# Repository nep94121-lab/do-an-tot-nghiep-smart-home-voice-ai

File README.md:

# Smart Home Voice AI (`v3.8.0` / `v1.0`) — Trợ Lý Nhà Thông Minh Giọng Nói Tiếng Việt

> **TRẠNG THÁI HOÀN THIỆN HỆ THỐNG — SẴN SÀNG CẮM PHẦN CỨNG LÀ CHẠY:**
> Toàn bộ **máy chủ Backend FastAPI (`backend/`)**, **giao diện Web 3D Digital Twin & Mobile PWA (`web/`)**, **ứng dụng Android gốc (`app/`)** và **firmware ESP8266 (`firmware/`)** đã **hoàn thiện 100%** và được kiểm thử đầy đủ.
> **Chỉ còn duy nhất bước cuối cùng ở hiện trường:** cắm bo mạch **NodeMCU ESP8266 v2 Amica** thật qua cáp Micro-USB, chạy **1 lệnh PowerShell** nạp firmware & nhập Wi-Fi lúc chạy (runtime, lưu vào LittleFS, không bao giờ lưu mật khẩu trong mã nguồn), gắn lên mạch **PCB Hub DIY v3** và cấp nguồn `5V 2A` là hệ thống hoạt động hoàn chỉnh.
>
> **Hướng dẫn nạp USB & cài Wi-Fi runtime thống nhất (Đọc ngay tại đây):**
> [`docs/huong_dan/CAI_DAT_WIFI_VA_NAP_USB.md`](docs/huong_dan/CAI_DAT_WIFI_VA_NAP_USB.md)

Trợ lý AI điều khiển nhà thông minh phản hồi tức thì bằng **100% tiếng Việt** (giọng `Aoede` duy nhất trên `gemini-3.8-live`), tích hợp **FastAPI Backend (`v3.8.0`) + SQLite WAL (25 bảng)**, **Web 3D Digital Twin (Three.js `r128`)**, **ứng dụng Android gốc (Kotlin + Jetpack Compose)**, **phần cứng PCB-Direct Hub DIY v3 (`100 × 80 × 1.6 mm`, không dùng breadboard trắng)** cùng **NodeMCU ESP8266 v2 Amica (`48.26 × 25.40 mm`, CP2102)** và **bộ vỏ nhà in 3D lắp mộng `agyhw14` (`16` bàn in, `660.64 g` PLA)**.

---

## 1. Hợp Đồng Phần Cứng Khóa Cứng (14 Module Vật Lý $\rightarrow$ 6 Thiết Bị + 3 Cảm Biến)

Hệ thống gồm **14 khối/module vật lý ngoài bo** (cộng `NodeMCU v2 Amica` và `PCB Hub DIY v3` thành `16` thành phần trong mô hình 3D) ánh xạ sang đúng **6 thiết bị chấp hành + 3 cảm biến** trên 10 chân **NodeMCU ESP8266 v2 Amica (`48.26 × 25.40 mm`, hàng chân `0.9"` — không dùng v3 LoLin)** cắm trực tiếp lên mạch **PCB Hub DIY v3 (`100 × 80 × 1.6 mm`, `51 footprints`, `0 ERC / 0 DRC`)** với **toàn bộ `C1–C9` (gồm `C8 100 nF` & `C9 100 µF 16V`) và `D1–D2 (1N4007)` hàn trực tiếp trên PCB**, cùng **40/40 dây nối `<= 30 cm` (`3.84 – 27.48 cm`)**.
**Chính sách phạm vi chốt:** **Không dùng breadboard trắng; không hỗ trợ quạt (`fan`), điều hòa (`ac`) hay hồng ngoại (`IR` / `VS1838B`).** Xem bảng ánh xạ chi tiết 14 module tại [`docs/phan_cung/TONG_QUAN_PHAN_CUNG_VA_IN_3D.md`](docs/phan_cung/TONG_QUAN_PHAN_CUNG_VA_IN_3D.md).

| Loại | Mã định danh | Tên hiển thị & Khối vật lý đi kèm | Chân ESP8266 | Quyền tối thiểu |
| :--- | :--- | :--- | :---: | :--- |
| Thiết bị | `main_door` | Cửa chính (Servo SG90 đồng trục không vít/keo) | `D1` (`GPIO5`) | Cấp 1 (Chủ nhà) |
| Thiết bị | `alarm_siren` | Còi báo động (Buzzer 5V `TMB12A05` + `Q1 S8050` + `D2`) | `D8` (`GPIO15`) | Cấp 1 (Chủ nhà) |
| Thiết bị | `garden_pump` | Bơm tưới cây (Relay 1 xanh 5V + Bơm chìm 3–6V + `D1`) | `D6` (`GPIO12`) | Cấp 2 (Thành viên) |
| Thiết bị | `speaker_amp` | Loa phản hồi (Relay 2 opto đỏ + `PAM8403` + Loa `28mm` + PWM `D3`) | `D7` (`GPIO13`) | Cấp 2 (Thành viên) |
| Thiết bị | `living_room_light` | Đèn phòng khách (LED 5mm + `R1 220Ω`) | `D0` (`GPIO16`) | Cấp 3 (Khách) |
| Thiết bị | `bedroom_light` | Đèn phòng ngủ (LED 5mm Active-LOW + `R2 220Ω` + `R7 10kΩ`) | `D4` (`GPIO2`) | Cấp 3 (Khách) |
| Cảm biến | `dht11` | Nhiệt độ (°C) & Độ ẩm không khí (%) (`DHT11` 3 chân) | `D2` (`GPIO4`) | Mọi cấp đã đăng nhập |
| Cảm biến | `soil_moisture` | Độ ẩm đất (`LM393` cấp `3.3V` + đầu dò `YL-69`) | `A0` (`ADC0`) | Mọi cấp đã đăng nhập |
| Cảm biến | `ky037` | Cảm biến âm thanh / tiếng vỗ tay (`KY-037/038 DO`, `3.3V`) | `D5` (`GPIO14`) | Mọi cấp đã đăng nhập |

---

## 2. Cấu Trúc Thư Mục Dự Án

Giữ nguyên toàn bộ các thư mục mã nguồn cốt lõi và tổ chức gọn tầng tài liệu theo nhóm chức năng rõ ràng:

```text
.
├── backend/                     # FastAPI v3.8.0, SQLite WAL (25 bảng), MQTT, SSE/WS, RBAC 3 tầng, Gemini Live Voice AI
├── web/                         # Web Dashboard 3D Digital Twin (Three.js r128), Mobile PWA (/app), /wokwi, /automation, /auth, /logs
├── app/                         # Ứng dụng Android gốc (Kotlin 2.3.20 + Jetpack Compose 1.10.4, minSdk 26, Lightbuild)
├── firmware/                    # Firmware NodeMCU ESP8266 v2 Amica (LittleFS Wi-Fi runtime + Offline FSM A1–A4) & Wokwi
├── hardware/
│   ├── flash_and_setup.ps1      # Script 1 lệnh nạp USB + nhập Wi-Fi runtime an toàn (ẩn mật khẩu) + SELF_TEST
│   ├── wiring_contract.py       # SSOT 40 dây nối, 15 đầu nối PCB J1–J15 & linh kiện bảo vệ C1–C9, D1–D2
│   ├── component_dimensions_ssot.py # SSOT kích thước datasheet 14 module + 2 bo lõi & thông số Servo SG90
│   ├── wire_lengths.json        # Chiều dài 3D thực tế 40/40 dây <= 30 cm (3.84–27.48 cm)
│   ├── kicad/                   # PCB Hub DIY v3 (100×80×1.6 mm, 51 footprints, 0 ERC / 0 DRC) & lắp ghép 3D
│   ├── mica/                    # Thiết kế vỏ nhà Mica 3mm cắt laser (FreeCAD 1.1.4)
│   ├── in 3 d/                  # Bộ in 3D v2 nhẹ hóa agyhw14: 16 bàn .3mf nhúng sẵn cấu hình, 660.64 g PLA, 0 support
│   └── blender/                 # Cảnh 3D tổng thể & 40 tuyến dây nối (Blender 5.2.2 LTS)
├── docs/
│   ├── kien_truc/               # Kiến trúc hệ thống (Mermaid), Công nghệ & Phiên bản thực đo, ERD SQLite 25 bảng, Repo Map
│   ├── huong_dan/               # Hướng dẫn thống nhất nạp USB & Wi-Fi runtime, Vận hành & Triển khai Production
│   ├── phan_cung/               # Tổng quan phần cứng & In 3D, WIRING_TABLE, WIRE_LIST_LENGTHS, DIMENSIONS_AUDIT, diy_pcb/, mica/
│   ├── bao_cao/                 # Hồ sơ Báo cáo Đồ án Tốt nghiệp (.docx / .pdf / script sinh / LOGO_SOURCES.md)
│   ├── luu_tru/                 # Tài liệu khảo sát & lịch sử giai đoạn đầu (chỉ lưu trữ, không dùng vận hành)
│   ├── screenshots/             # 13 ảnh chụp màn hình kiểm chứng Web, Mobile PWA, Android & Sơ đồ 2D
│   ├── HARDWARE_BUILD_GUIDE.md  # Chỉ mục chế tạo PCB-direct, cắt Mica / In 3D & đấu nối
│   └── TIER_PERMISSIONS.md      # Bảng phân quyền 3 tầng khóa cứng cho 6 thiết bị
├── tests/                       # Bộ kiểm thử tự động pytest (Backend, RBAC, Voice agyfix11, PCB/In 3D agyhw12–14)
├── scripts/                     # Tiện ích sinh tài liệu dây nối, kiểm định kích thước & công cụ bảo trì
├── specs/                       # Đặc tả kỹ thuật tham chiếu
├── test_audio/                  # Bộ mẫu âm thanh tiếng Việt kiểm thử giọng nói
├── USER_GUIDE.md                # Hướng dẫn sử dụng chi tiết cho người dùng cuối
├── KE_HOACH_DO_AN_TOT_NGHIEP.md # Hồ sơ tiến độ & trạng thái hoàn thiện đồ án
├── KNOWN_ISSUES.md              # Danh mục vấn đề nhỏ đã biết & giải pháp tạm thời
└── CHANGELOG.md                 # Nhật ký phát hành các phiên bản
```

---

## 3. Chỉ Mục Toàn Bộ Tài Liệu Dự Án

| Nhóm tài liệu | Tài liệu | Nội dung chính |
| :--- | :--- | :--- |
| **Cắm phần cứng & Wi-Fi** | [**Hướng dẫn nạp Firmware USB & Cài Wi-Fi Runtime**](docs/huong_dan/CAI_DAT_WIFI_VA_NAP_USB.md) | Quy trình 3 bước cắm USB $\rightarrow$ chạy `hardware/flash_and_setup.ps1` nhập Wi-Fi lưu LittleFS `/wifi_config.json` $\rightarrow$ cấp nguồn chạy, driver CP2102/CH340, chân boot-strap `D3/D4/D8`, xử lý sự cố |
| **Người dùng cuối** | [Hướng dẫn sử dụng (`USER_GUIDE.md`)](USER_GUIDE.md) | Phân quyền 3 cấp, mã mời QR dùng 1 lần, Web 3D `/`, Mobile `/app`, Tự động hóa `/automation`, giọng nói tiếng Việt, ứng dụng Android, `/wokwi` & chế độ ngoại tuyến |
| **Kiến trúc & Phiên bản** | [Kiến trúc hệ thống chi tiết (`KIEN_TRUC_HE_THONG.md`)](docs/kien_truc/KIEN_TRUC_HE_THONG.md) | Kiến trúc toàn bộ phân hệ Backend, SQLite WAL, MQTT, SSE/WS, Web 3D, Android, ESP8266, Gemini Live `agyfix11`, RBAC & 4 sơ đồ tuần tự Mermaid |
| **Kiến trúc & Phiên bản** | [Công nghệ & Phiên bản phần mềm (`CONG_NGHE_VA_PHIEN_BAN.md`)](docs/kien_truc/CONG_NGHE_VA_PHIEN_BAN.md) | Bảng phiên bản thực đo đầy đủ của Python, FastAPI, SQLite, Three.js, Kotlin/Compose, PlatformIO, KiCad, FreeCAD, Blender, PrusaSlicer, Playwright, Tailscale, Vercel |
| **Kiến trúc & Phiên bản** | [Sơ đồ CSDL SQLite 25 bảng (`DATABASE_SCHEMA_ERD.md`)](docs/kien_truc/DATABASE_SCHEMA_ERD.md) | Sơ đồ thực thể kết hợp (ERD Mermaid) đủ 25 bảng 3NF và cơ chế cách ly 2 bể tự động hóa |
| **Kiến trúc & Phiên bản** | [Bảng phân quyền 3 tầng (`docs/TIER_PERMISSIONS.md`)](docs/TIER_PERMISSIONS.md) · [Bản đồ mã nguồn (`REPO_MAP.md`)](docs/kien_truc/REPO_MAP.md) | Ma trận quyền 3 cấp khóa cứng 6 thiết bị & chỉ mục cấu trúc mã nguồn hiện hành |
| **Vận hành & Triển khai** | [Hướng dẫn vận hành & triển khai (`VAN_HANH_VA_TRIEN_KHAI.md`)](docs/huong_dan/VAN_HANH_VA_TRIEN_KHAI.md) | Biến môi trường `.env` (chỉ tên biến), chạy cổng `8088`, Tailscale Funnel, Vercel redirect, backup/restore SQLite WAL, `DEPLOY.lock`, quy trình `pytest` + Playwright + Android APK |
| **Phần cứng & In 3D** | [Tổng quan phần cứng 14 module & In 3D (`TONG_QUAN_PHAN_CUNG_VA_IN_3D.md`)](docs/phan_cung/TONG_QUAN_PHAN_CUNG_VA_IN_3D.md) | Bảng ánh xạ SSOT 14 module vật lý + 2 bo lõi sang 6 thiết bị + 3 cảm biến, PCB Hub DIY v3, 40 dây `<= 30 cm`, bộ in 3D 16 bàn `660.64 g` |
| **Phần cứng & In 3D** | [Chỉ mục chế tạo phần cứng (`docs/HARDWARE_BUILD_GUIDE.md`)](docs/HARDWARE_BUILD_GUIDE.md) · [Bảng 40 dây (`WIRING_TABLE.md`)](docs/phan_cung/WIRING_TABLE.md) · [Chiều dài dây (`WIRE_LIST_LENGTHS.md`)](docs/phan_cung/WIRE_LIST_LENGTHS.md) | Hồ sơ gia công KiCad [`diy_pcb/`](docs/phan_cung/diy_pcb/), kiểm định kích thước [`DIMENSIONS_AUDIT.md`](docs/phan_cung/DIMENSIONS_AUDIT.md), linh kiện [`DANH_SACH_LINH_KIEN_HIEN_CO_VA_CAN_MUA.md`](docs/phan_cung/DANH_SACH_LINH_KIEN_HIEN_CO_VA_CAN_MUA.md), bộ in 3D [`hardware/in 3 d/README.md`](hardware/in%203%20d/README.md) |
| **Firmware ESP8266** | [Tài liệu Firmware (`firmware/README.md`)](firmware/README.md) · [Bản nạp USB cho `/wokwi`](docs/phan_cung/HUONG_DAN_NAP_FIRMWARE_USB.md) | Chi tiết sơ đồ 10 chân boot-safe và cơ chế dự phòng ngoại tuyến Addendum A1–A4 |
| **Quản trị & Lịch sử** | [Hồ sơ Đồ án (`KE_HOACH_DO_AN_TOT_NGHIEP.md`)](KE_HOACH_DO_AN_TOT_NGHIEP.md) · [Vấn đề đã biết (`KNOWN_ISSUES.md`)](KNOWN_ISSUES.md) · [Nhật ký (`CHANGELOG.md`)](CHANGELOG.md) · [Kho lưu trữ cũ (`docs/luu_tru/`)](docs/luu_tru/README.md) | Trạng thái hoàn thiện tổng thể, danh mục giới hạn nhỏ fail-closed, lịch sử phát hành và tài liệu khảo sát giai đoạn đầu |

---

## 4. Khởi Chạy Nhanh (Quick Start)

### 4.1. Cài đặt phụ thuộc & khởi động máy chủ Backend (`:8088`)
```powershell
pip install -r requirements.txt
# Tạo tệp .env ở thư mục gốc (không commit Git) với GEMINI_API_KEY (xem VAN_HANH_VA_TRIEN_KHAI.md)
python -X utf8 -m uvicorn backend.server:app --host 0.0.0.0 --port 8088
```
Truy cập trình duyệt tại `http://127.0.0.1:8088/` (máy tính) hoặc `http://127.0.0.1:8088/app` (di động).

### 4.2. Nạp Firmware ESP8266 & cấu hình Wi-Fi Runtime qua USB (1 lệnh)
```powershell
# Kiểm tra toolchain PlatformIO, driver CP210x/CH340, cổng COM và biên dịch khô (không nạp)
powershell -NoProfile -ExecutionPolicy Bypass -File hardware\flash_and_setup.ps1 -DryRun

# Cắm NodeMCU ESP8266 qua cáp Micro-USB, nạp firmware + nhập Wi-Fi runtime ẩn mật khẩu + SELF_TEST
powershell -NoProfile -ExecutionPolicy Bypass -File hardware\flash_and_setup.ps1
```
Xem chi tiết từng bước và bảng khắc phục sự cố tại [`docs/huong_dan/CAI_DAT_WIFI_VA_NAP_USB.md`](docs/huong_dan/CAI_DAT_WIFI_VA_NAP_USB.md).

### 4.3. Biên dịch ứng dụng Android (`app/`) & chạy kiểm thử (`pytest`)
```powershell
# Biên dịch ứng dụng Android gốc (Kotlin 2.3.20 + Jetpack Compose, minSdk 26)
Set-Location app
lightbuild --plain build app

# Kiểm thử hồi quy phần cứng, PCB-Direct, Servo và In 3D (chạy tại thư mục gốc)
python -m pytest -q --timeout=120 \
  tests/test_hw_contract_6devices_20261120.py \
  tests/test_pcbdirect_agyhw12.py \
  tests/test_servodoor_agyhw13.py \
  tests/test_lessplastic_agyhw14.py
```

### 4.4. Tóm tắt Phần cứng PCB-Direct & Bộ In 3D `agyhw14`
- **PCB Hub DIY v3 (`100 × 80 × 1.6 mm`, 1 lớp `B.Cu`, không dùng breadboard trắng):** `51 footprints`, `0 ERC / 0 DRC`, toàn bộ `C1–C9` & `D1–D2` hàn trực tiếp trên bo.
- **Hệ thống dây nối (`40/40 <= 30 cm`):** Ngắn nhất `3.84 cm`, dài nhất `27.48 cm`, tổng `654.99 cm` (`10` sợi 10 cm, `18` sợi 20 cm, `12` sợi 30 cm).
- **Vỏ nhà In 3D v2 (`agyhw14`, `180×200×250 mm`):** **`16` bàn in `.3mf`** nhúng sẵn thông số (`9% Gyroid`, `2/3` thành, `0% support`), **`51` chi tiết / `83` bản thể**, **`660.64 g` PLA** (`-36.77%` so với `1044.86 g`), thời gian in `73g 23p 49s`, `0` va chạm 3D BRep, cơ cấu cửa Servo SG90 đồng trục dự trữ mô-men `14.56×`.

---

## 5. Thư Viện Ảnh Chụp Kiểm Chứng (`docs/screenshots/`)

| Ảnh chụp (`docs/screenshots/`) | Nội dung minh họa |
| :--- | :--- |
| [`01_dashboard_3d_desktop_1440x900.png`](docs/screenshots/01_dashboard_3d_desktop_1440x900.png) | Giao diện Web Dashboard 3D Digital Twin & 6 thiết bị (`1440×900`) |
| [`02_dashboard_3d_desktop_1366x768.png`](docs/screenshots/02_dashboard_3d_desktop_1366x768.png) | Giao diện Web Dashboard 3D Digital Twin trên màn hình laptop (`1366×768`) |
| [`03_dashboard_3d_mobile_390x844.png`](docs/screenshots/03_dashboard_3d_mobile_390x844.png) | Giao diện Web Dashboard đáp ứng di động (`390×844`) |
| [`04_automation_panel_1440x900.png`](docs/screenshots/04_automation_panel_1440x900.png) | Trang Tự động hóa (`/automation`): luật tổ hợp `AND`/`OR`, lịch tuần & hẹn giờ |
| [`05_wokwi_circuit_1440x900.png`](docs/screenshots/05_wokwi_circuit_1440x900.png) | Trang Hướng dẫn Đấu nối PCB-Direct 10 chân ESP8266 & PCB Hub `100×80 mm` (`/wokwi`) |
| [`06_auth_rbac_1440x900.png`](docs/screenshots/06_auth_rbac_1440x900.png) | Trang Quản lý Phiên & Phân quyền 3 tầng (`/auth`) |
| [`07_logs_audit_1440x900.png`](docs/screenshots/07_logs_audit_1440x900.png) | Trang Nhật ký Hệ thống dành riêng cho Chủ nhà Cấp 1 (`/logs`) |
| [`08_mobile_pwa_390x844.png`](docs/screenshots/08_mobile_pwa_390x844.png) | Giao diện Ứng dụng Web Di động PWA (`/app`, `390×844`) |
| [`09_android_auth_gate.png`](docs/screenshots/09_android_auth_gate.png) | Ứng dụng Android gốc: cổng xác thực khi chưa đăng nhập & nút Quét mã QR |
| [`10_android_home_live.png`](docs/screenshots/10_android_home_live.png) | Ứng dụng Android gốc: màn hình chính & thẻ thông số cảm biến thời gian thực |
| [`11_android_devices_6locked.png`](docs/screenshots/11_android_devices_6locked.png) | Ứng dụng Android gốc: danh sách 6 thiết bị chấp hành theo hợp đồng khóa cứng |
| [`12_android_voice_vi.png`](docs/screenshots/12_android_voice_vi.png) | Ứng dụng Android gốc: trợ lý giọng nói tiếng Việt đồng bộ máy chủ |
| [`13_hardware_wiring_2d.png`](docs/screenshots/13_hardware_wiring_2d.png) | Sơ đồ đấu nối tổng thể 2D PCB-Direct 40 dây & 15 đầu nối PCB Hub DIY v3 (`100×80 mm`) |

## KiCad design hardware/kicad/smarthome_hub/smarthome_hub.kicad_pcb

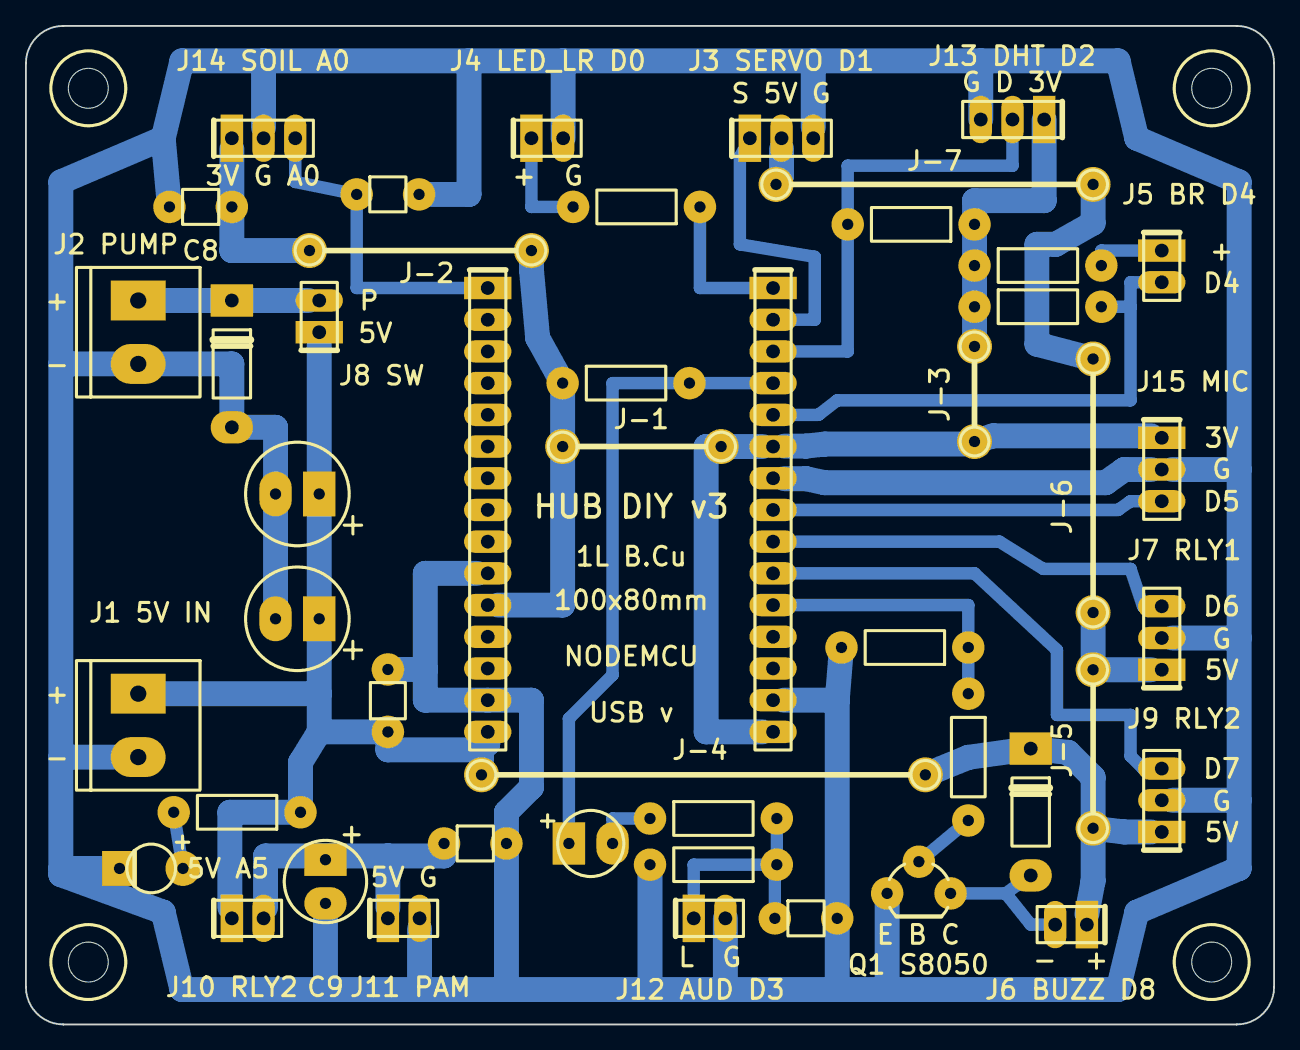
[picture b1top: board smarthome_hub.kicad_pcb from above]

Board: 2 copper layers, 100.0 x 80.0 mm, 51 parts (0 on the bottom side), 29 nets.

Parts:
C1, C2: 470uF 16V; CP_Radial_D8.0mm_P3.50mm_DIY
C3, C6, C7, C8: 100nF; C_Disc_D5.0mm_P5.00mm_DIY
C4: 10uF 16V; CP_Radial_D5.0mm_P3.50mm_DIY
C5: 10nF; C_Disc_D5.0mm_P5.00mm_DIY
C9: 100uF 16V; CP_Radial_D6.3mm_P3.50mm_DIY
D1, D2: 1N4007; D_DO41_P10.16mm_DIY
D3: LED_PWR_GRN; LED_D3.0mm_P5.08mm_DIY
H1, H2, H3, H4: M3_3.2mm; MountingHole_3.2mm_M3_DIY
J1: PWR_5V_IN; TerminalBlock_MKDS_1x02_P5.08mm_DIY
J2: PUMP_OUT; TerminalBlock_MKDS_1x02_P5.08mm_DIY
J3: SERVO_D1; PinHeader_1x03_P2.54mm_DIY
J4: LED_LR_D0; PinHeader_1x02_P2.54mm_DIY
J5: LED_BR_D4; PinHeader_1x02_P2.54mm_DIY
J6: BUZZ_D8; PinHeader_1x02_P2.54mm_DIY
J7: RLY1_PUMP_D6; PinHeader_1x03_P2.54mm_DIY
J8: RLY1_SW; PinHeader_1x02_P2.54mm_DIY
J9: RLY2_AMP_D7; PinHeader_1x03_P2.54mm_DIY
J10: RLY2_SW; PinHeader_1x02_P2.54mm_DIY
J11: PAM8403_PWR; PinHeader_1x02_P2.54mm_DIY
J12: AUDIO_D3; PinHeader_1x02_P2.54mm_DIY
J13: DHT11_D2; PinHeader_1x03_P2.54mm_DIY
J14: SOIL_A0; PinHeader_1x03_P2.54mm_DIY
J15: KY037_D5; PinHeader_1x03_P2.54mm_DIY
JP1, JP5: JUMPER_12.70mm; WireJumper_P12.70mm_DIY
JP2: JUMPER_17.78mm; WireJumper_P17.78mm_DIY
JP3: JUMPER_7.62mm; WireJumper_P7.62mm_DIY
JP4: JUMPER_35.56mm; WireJumper_P35.56mm_DIY
JP6: JUMPER_20.32mm; WireJumper_P20.32mm_DIY
JP7: JUMPER_25.40mm; WireJumper_P25.40mm_DIY
Q1: S8050; TO-92_Wide_DIY
R1, R2: 220R; R_Axial_P10.16mm_DIY
R3, R4, R7, R9: 10k; R_Axial_P10.16mm_DIY
R5, R6: 2.2k; R_Axial_P10.16mm_DIY
R8, R10: 1k; R_Axial_P10.16mm_DIY
U1: NodeMCU_Left_1x15; PinSocket_1x15_P2.54mm_DIY
U2: NodeMCU_Right_1x15; PinSocket_1x15_P2.54mm_DIY

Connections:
+3V3: JP1.1, JP2.1, R4.1, U1.11
+5V: C1.1, C2.1, C3.1, J1.1, J8.1, J10.1, JP4.1, R8.1, U1.15
/+3V3_R: J15.1, JP1.2, JP3.1, U2.6, U2.15
/+3V3_SOIL: C8.1, J14.1, JP2.2
/+3V3_TOP: J13.1, JP3.2, R2.1, R3.1, R7.1
/+5V_RLY1: J7.1, JP5.2, JP6.1
/+5V_RLY2: D2.1, J6.1, J9.1, JP4.2, JP5.1
/+5V_SERVO: J3.2, JP7.2
/+5V_TOP: JP6.2, JP7.1
/A0_SOIL: C7.1, J14.3, U1.1
/AMP_5V: C6.1, C9.1, J10.2, J11.1
/AUD_OUT: C5.1, J12.1, R5.2, R6.1
/BUZZ_BASE: Q1.2, R10.2
/BUZZ_K: D2.2, J6.2, Q1.3
/D0_LED_LR: R1.1, U2.1
/D1_SERVO: J3.1, U2.2
/D2_DHT11: J13.2, R3.2, U2.3
/D3_AUDIO_PWM: C4.1, R4.2, U2.4
/D4_LED_BR: J5.2, R7.2, U2.5
/D5_MIC_DO: J15.3, U2.8
/D6_RLY1_PUMP: J7.3, U2.9
/D7_RLY2_AMP: J9.3, U2.10
/D8_BUZZER: R9.1, R10.1, U2.11
/PUMP_5V: D1.1, J2.1, J8.2
GND: C1.2, C2.2, C3.2, C5.2, C6.2, C7.2, C8.2, C9.2, D1.2, D3.1, J1.2, J2.2, J3.3, J4.2, J7.2, J9.2, J11.2, J12.2, J13.3, J14.2, J15.2, Q1.1, R6.2, R9.2, U1.10, U1.14, U2.7, U2.14
unnamed: C4.2, R5.1
unnamed: D3.2, R8.2
unnamed: J4.1, R1.2
unnamed: J5.1, R2.2

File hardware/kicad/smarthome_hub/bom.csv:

"Refs","Value","Footprint","Qty","DNP"
"C1","470uF 16V","DIY_Hub:CP_Radial_D8.0mm_P3.50mm_DIY","1",""
"C2","470uF 16V","DIY_Hub:CP_Radial_D8.0mm_P3.50mm_DIY","1",""
"C3","100nF","DIY_Hub:C_Disc_D5.0mm_P5.00mm_DIY","1",""
"C4","10uF 16V","DIY_Hub:CP_Radial_D5.0mm_P3.50mm_DIY","1",""
"C5","10nF","DIY_Hub:C_Disc_D5.0mm_P5.00mm_DIY","1",""
"C6","100nF","DIY_Hub:C_Disc_D5.0mm_P5.00mm_DIY","1",""
"C7","100nF","DIY_Hub:C_Disc_D5.0mm_P5.00mm_DIY","1",""
"C8","100nF","DIY_Hub:C_Disc_D5.0mm_P5.00mm_DIY","1",""
"C9","100uF 16V","DIY_Hub:CP_Radial_D6.3mm_P3.50mm_DIY","1",""
"D1","1N4007","DIY_Hub:D_DO41_P10.16mm_DIY","1",""
"D2","1N4007","DIY_Hub:D_DO41_P10.16mm_DIY","1",""
"D3","LED_PWR_GRN","DIY_Hub:LED_D3.0mm_P5.08mm_DIY","1",""
"H1","M3_3.2mm","DIY_Hub:MountingHole_3.2mm_M3_DIY","1",""
"H2","M3_3.2mm","DIY_Hub:MountingHole_3.2mm_M3_DIY","1",""
"H3","M3_3.2mm","DIY_Hub:MountingHole_3.2mm_M3_DIY","1",""
"H4","M3_3.2mm","DIY_Hub:MountingHole_3.2mm_M3_DIY","1",""
"J1","PWR_5V_IN","DIY_Hub:TerminalBlock_MKDS_1x02_P5.08mm_DIY","1",""
"J2","PUMP_OUT","DIY_Hub:TerminalBlock_MKDS_1x02_P5.08mm_DIY","1",""
"J3","SERVO_D1","DIY_Hub:PinHeader_1x03_P2.54mm_DIY","1",""
"J4","LED_LR_D0","DIY_Hub:PinHeader_1x02_P2.54mm_DIY","1",""
"J5","LED_BR_D4","DIY_Hub:PinHeader_1x02_P2.54mm_DIY","1",""
"J6","BUZZ_D8","DIY_Hub:PinHeader_1x02_P2.54mm_DIY","1",""
"J7","RLY1_PUMP_D6","DIY_Hub:PinHeader_1x03_P2.54mm_DIY","1",""
"J8","RLY1_SW","DIY_Hub:PinHeader_1x02_P2.54mm_DIY","1",""
"J9","RLY2_AMP_D7","DIY_Hub:PinHeader_1x03_P2.54mm_DIY","1",""
"J10","RLY2_SW","DIY_Hub:PinHeader_1x02_P2.54mm_DIY","1",""
"J11","PAM8403_PWR","DIY_Hub:PinHeader_1x02_P2.54mm_DIY","1",""
"J12","AUDIO_D3","DIY_Hub:PinHeader_1x02_P2.54mm_DIY","1",""
"J13","DHT11_D2","DIY_Hub:PinHeader_1x03_P2.54mm_DIY","1",""
"J14","SOIL_A0","DIY_Hub:PinHeader_1x03_P2.54mm_DIY","1",""
"J15","KY037_D5","DIY_Hub:PinHeader_1x03_P2.54mm_DIY","1",""
"JP1","JUMPER_12.70mm","DIY_Hub:WireJumper_P12.70mm_DIY","1",""
"JP2","JUMPER_17.78mm","DIY_Hub:WireJumper_P17.78mm_DIY","1",""
"JP3","JUMPER_7.62mm","DIY_Hub:WireJumper_P7.62mm_DIY","1",""
"JP4","JUMPER_35.56mm","DIY_Hub:WireJumper_P35.56mm_DIY","1",""
"JP5","JUMPER_12.70mm","DIY_Hub:WireJumper_P12.70mm_DIY","1",""
"JP6","JUMPER_20.32mm","DIY_Hub:WireJumper_P20.32mm_DIY","1",""
"JP7","JUMPER_25.40mm","DIY_Hub:WireJumper_P25.40mm_DIY","1",""
"Q1","S8050","DIY_Hub:TO-92_Wide_DIY","1",""
"R1","220R","DIY_Hub:R_Axial_P10.16mm_DIY","1",""
"R2","220R","DIY_Hub:R_Axial_P10.16mm_DIY","1",""
"R3","10k","DIY_Hub:R_Axial_P10.16mm_DIY","1",""
"R4","10k","DIY_Hub:R_Axial_P10.16mm_DIY","1",""
"R5","2.2k","DIY_Hub:R_Axial_P10.16mm_DIY","1",""
"R6","2.2k","DIY_Hub:R_Axial_P10.16mm_DIY","1",""
"R7","10k","DIY_Hub:R_Axial_P10.16mm_DIY","1",""
"R8","1k","DIY_Hub:R_Axial_P10.16mm_DIY","1",""
"R9","10k","DIY_Hub:R_Axial_P10.16mm_DIY","1",""
"R10","1k","DIY_Hub:R_Axial_P10.16mm_DIY","1",""
"U1","NodeMCU_Left_1x15","DIY_Hub:PinSocket_1x15_P2.54mm_DIY","1",""
"U2","NodeMCU_Right_1x15","DIY_Hub:PinSocket_1x15_P2.54mm_DIY","1",""

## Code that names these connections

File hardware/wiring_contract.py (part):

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
    # --- Device 1: Main Door Servo SG90 (J3 -> SG90) ---
    WireEntry("W03", "Main Door (SG90)", "J3", "1", "J3.1 (SERVO_D1)", "Orange",
              "sg90_servo", "SG90 Micro Servo", "PWM (Orange)", "D1 (U2.2)", "GPIO5", "D1_SERVO",
              "esp8266_smarthome.ino:56", "Dupont 1x3 F-M",
              "50Hz PWM control: 0 deg closed / 90 deg open (main_door)"),
    WireEntry("W04", "Main Door (SG90)", "J3", "2", "J3.2 (SERVO_D1)", "Red",
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              "esp8266_smarthome.ino:59,68", "Dupont 1x2 F-F",
              "Current-limited +3.3V via on-board R2 220R for boot-safe Active-LOW LED"),
    WireEntry("W09", "Bedroom LED", "J5", "2", "J5.2 (LED_BR_D4)", "White",
              "led_bedroom", "5mm LED (Bedroom)", "Cathode (-)", "D4 (U2.5)", "GPIO2", "D4_LED_BR",
              "esp8266_smarthome.ino:59,68", "Dupont 1x2 F-F",
              "Active-LOW sink (BEDROOM_LED_ACTIVE_LOW=true); on-board R7 10k pull-up keeps GPIO2 HIGH at boot"),

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              "esp8266_smarthome.ino:61,70", "Dupont 1x3 F-F",
              "Relay 1 module logic/coil ground"),
    WireEntry("W12", "Garden Pump (Relay 1)", "J7", "3", "J7.3 (RLY1_PUMP_D6)", "Green",
              "relay1_pump", "Relay 1 (Blue 5V 1-ch)", "IN", "D6 (U2.9)", "GPIO12", "D6_RLY1_PUMP",
              "esp8266_smarthome.ino:61,70", "Dupont 1x3 F-F",
              "Relay 1 trigger input (PUMP_RELAY_ACTIVE_LOW=false, active-HIGH)"),
    WireEntry("W13", "Garden Pump (Relay 1)", "J8", "1", "J8.1 (RLY1_SW)", "Red",
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              "esp8266_smarthome.ino:63,399", "Dupont 1x2 F-F",
              "+5V supply to TMB12A05 buzzer anode; protected by on-board D2 1N4007 flyback across J6.1-J6.2"),
    WireEntry("W18", "Alarm Siren (Buzzer)", "J6", "2", "J6.2 (BUZZ_D8)", "Orange",
              "buzzer_alarm", "Active 5V Buzzer (TMB12A05)", "Buzzer (-)", "D8 (U2.11) via Q1 S8050", "GPIO15 (NPN low-side)", "BUZZ_K",
              "esp8266_smarthome.ino:63,399", "Dupont 1x2 F-F",
              "Low-side switched by on-board Q1 (S8050 NPN) + R10 1k base resistor; R9 10k pull-down keeps GPIO15 LOW at boot"),

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              "esp8266_smarthome.ino:62,71", "Dupont 1x3 F-F",
              "Relay 2 module ground"),
    WireEntry("W21", "Speaker Amp (Relay 2)", "J9", "3", "J9.3 (RLY2_AMP_D7)", "Cyan",
              "relay2_speaker", "Relay 2 (Red Opto 5V, Jmp=H)", "IN", "D7 (U2.10)", "GPIO13", "D7_RLY2_AMP",
              "esp8266_smarthome.ino:62,71", "Dupont 1x3 F-F",
              "Active-HIGH trigger (SPEAKER_RELAY_ACTIVE_LOW=false); auto-off 1.5s after chime"),
    WireEntry("W22", "Speaker Amp (Relay 2)", "J10", "1", "J10.1 (RLY2_SW)", "Red",
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              "esp8266_smarthome.ino:62,163", "Dupont 1x2 F-F",
              "PAM8403 power ground"),
    WireEntry("W26", "Speaker Amp (Audio PWM)", "J12", "1", "J12.1 (AUDIO_D3)", "White",
              "pam8403_amp", "PAM8403 Audio Amplifier", "L (Audio In)", "D3 (U2.4) via C4/R5/R6/C5", "GPIO0", "AUD_OUT",
              "esp8266_smarthome.ino:58,166-184", "Dupont 1x2 F-F",
              "DC-blocked (C4 10uF) & RC-attenuated (R5/R6 2.2k, C5 10nF) audio; R4 10k pull-up + IDLE=INPUT for boot safety"),
    WireEntry("W27", "Speaker Amp (Audio PWM)", "J12", "2", "J12.2 (AUDIO_D3)", "Black",
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              "esp8266_smarthome.ino:57,83", "Dupont 1x3 F-F",
              "3.3V sensor supply"),
    WireEntry("W31", "DHT11 Sensor", "J13", "2", "J13.2 (DHT11_D2)", "Blue",
              "dht11_sensor", "DHT11 3-Pin Breakout", "DATA (OUT)", "D2 (U2.3)", "GPIO4", "D2_DHT11",
              "esp8266_smarthome.ino:57,83,544", "Dupont 1x3 F-F",
              "1-wire data bus with on-board R3 10k pull-up to +3V3"),
    WireEntry("W32", "DHT11 Sensor", "J13", "3", "J13.3 (DHT11_D2)", "Black",
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              "esp8266_smarthome.ino:14,60", "Dupont 1x3 F-F",
              "KY-037 ground (AO pin intentionally left NC / unconnected)"),
    WireEntry("W40", "Sound Sensor (KY-037)", "J15", "3", "J15.3 (KY037_D5)", "Yellow",
              "ky037_sound", "KY-037 / KY-038 Sound Module", "DO", "D5 (U2.8)", "GPIO14", "D5_MIC_DO",
              "esp8266_smarthome.ino:60,412", "Dupont 1x3 F-F",
              "Digital clap/loud-sound interrupt (RISING edge, debounce >= 400ms)"),
)
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        value="10µF",
        voltage_rating="16V",
        polarity="Có cực (+/-): chân (+) về D3 (GPIO0), chân (-) về R5 (AUD_AC)",
        placement_pins="Hàn trên PCB Hub nối tiếp U2.4 (D3_AUDIO_PWM) → R5 (AUD_AC, CP_Radial D5.0×P3.5mm)",
        net_pos="D3_AUDIO_PWM",
        net_neg="AUD_AC",
        role_vi="Tụ hóa chặn thành phần một chiều (DC-block), cô lập chân boot-strap D3 (GPIO0) khỏi ngõ vào PAM8403.",
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        value="10nF (103)",
        voltage_rating="50V",
        polarity="Không phân cực (tụ gốm)",
        placement_pins="Hàn trên PCB Hub tại nút J12.1 (AUD_OUT) ↔ GND (C_Disc D5.0×P5.0mm)",
        net_pos="AUD_OUT",
        net_neg="GND",
        role_vi="Tụ gốm lọc thông thấp RC (cùng R5/R6 2.2kΩ, fc ≈ 14.5 kHz) làm mịn tín hiệu PWM vào PAM8403.",
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        value="100nF (104)",
        voltage_rating="50V",
        polarity="Không phân cực (tụ gốm)",
        placement_pins="Hàn trên PCB Hub sát J11.1 (AMP_5V) ↔ J11.2 (GND) (C_Disc D5.0×P5.0mm)",
        net_pos="AMP_5V",
        net_neg="GND",
        role_vi="Tụ gốm lọc nhiễu cao tần trên nhánh nguồn +5V đóng cắt qua Rơ-le 2 cấp cho PAM8403.",
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        value="100nF (104)",
        voltage_rating="50V",
        polarity="Không phân cực (tụ gốm)",
        placement_pins="Hàn trên PCB Hub sát J14.3 (A0_SOIL) ↔ GND (C_Disc D5.0×P5.0mm)",
        net_pos="A0_SOIL",
        net_neg="GND",
        role_vi="Tụ gốm lọc nhiễu tương tự cho chân ADC0 (A0) đọc cảm biến độ ẩm đất LM393.",
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        value="100µF",
        voltage_rating="16V",
        polarity="Có cực (+/-): chân (+) nối AMP_5V (5V+), chân (-) vạch trắng nối GND (5V-)",
        placement_pins="Hàn trực tiếp trên PCB Hub ngay cạnh J11 (AMP_5V ↔ GND, CP_Radial D6.3×P3.5mm, song song C6 100nF cấp nguồn PAM8403)",
        net_pos="AMP_5V",
        net_neg="GND",
        role_vi="Tụ hóa dự trữ năng lượng hàn trên bo cho tầng khuếch đại Class-D PAM8403, giảm méo tiếng và sụt áp xung khi phát chuông loa 8Ω.",
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        value="1N4007",
        voltage_rating="1000V / 1A",
        polarity="Có cực (K/A): vạch bạc Cathode (K) nối PUMP_5V (+), Anode (A) nối GND (-)",
        placement_pins="Hàn trên PCB Hub mắc ngược song song ngõ ra bơm J2 (J2.1 PUMP_5V ↔ J2.2 GND, DO-41)",
        net_pos="PUMP_5V",
        net_neg="GND",
        role_vi="Diode dập xung ngược (Flyback) triệt xung cảm ứng khi Rơ-le 1 ngắt động cơ bơm 3–6V, bảo vệ tiếp điểm và ESP8266.",
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        value="1N4007",
        voltage_rating="1000V / 1A",
        polarity="Có cực (K/A): vạch bạc Cathode (K) nối +5V (J6.1), Anode (A) nối BUZZ_K / Q1.C (J6.2)",
        placement_pins="Hàn trên PCB Hub mắc ngược song song còi 5V tại J6 (J6.1 +5V ↔ J6.2 BUZZ_K / Q1 Collector, DO-41)",
        net_pos="+5V",
        net_neg="BUZZ_K",
        role_vi="Diode dập xung ngược (Flyback) bảo vệ transistor lái NPN Q1 (S8050) trước xung điện áp ngược từ cuộn dây còi TMB12A05.",
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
